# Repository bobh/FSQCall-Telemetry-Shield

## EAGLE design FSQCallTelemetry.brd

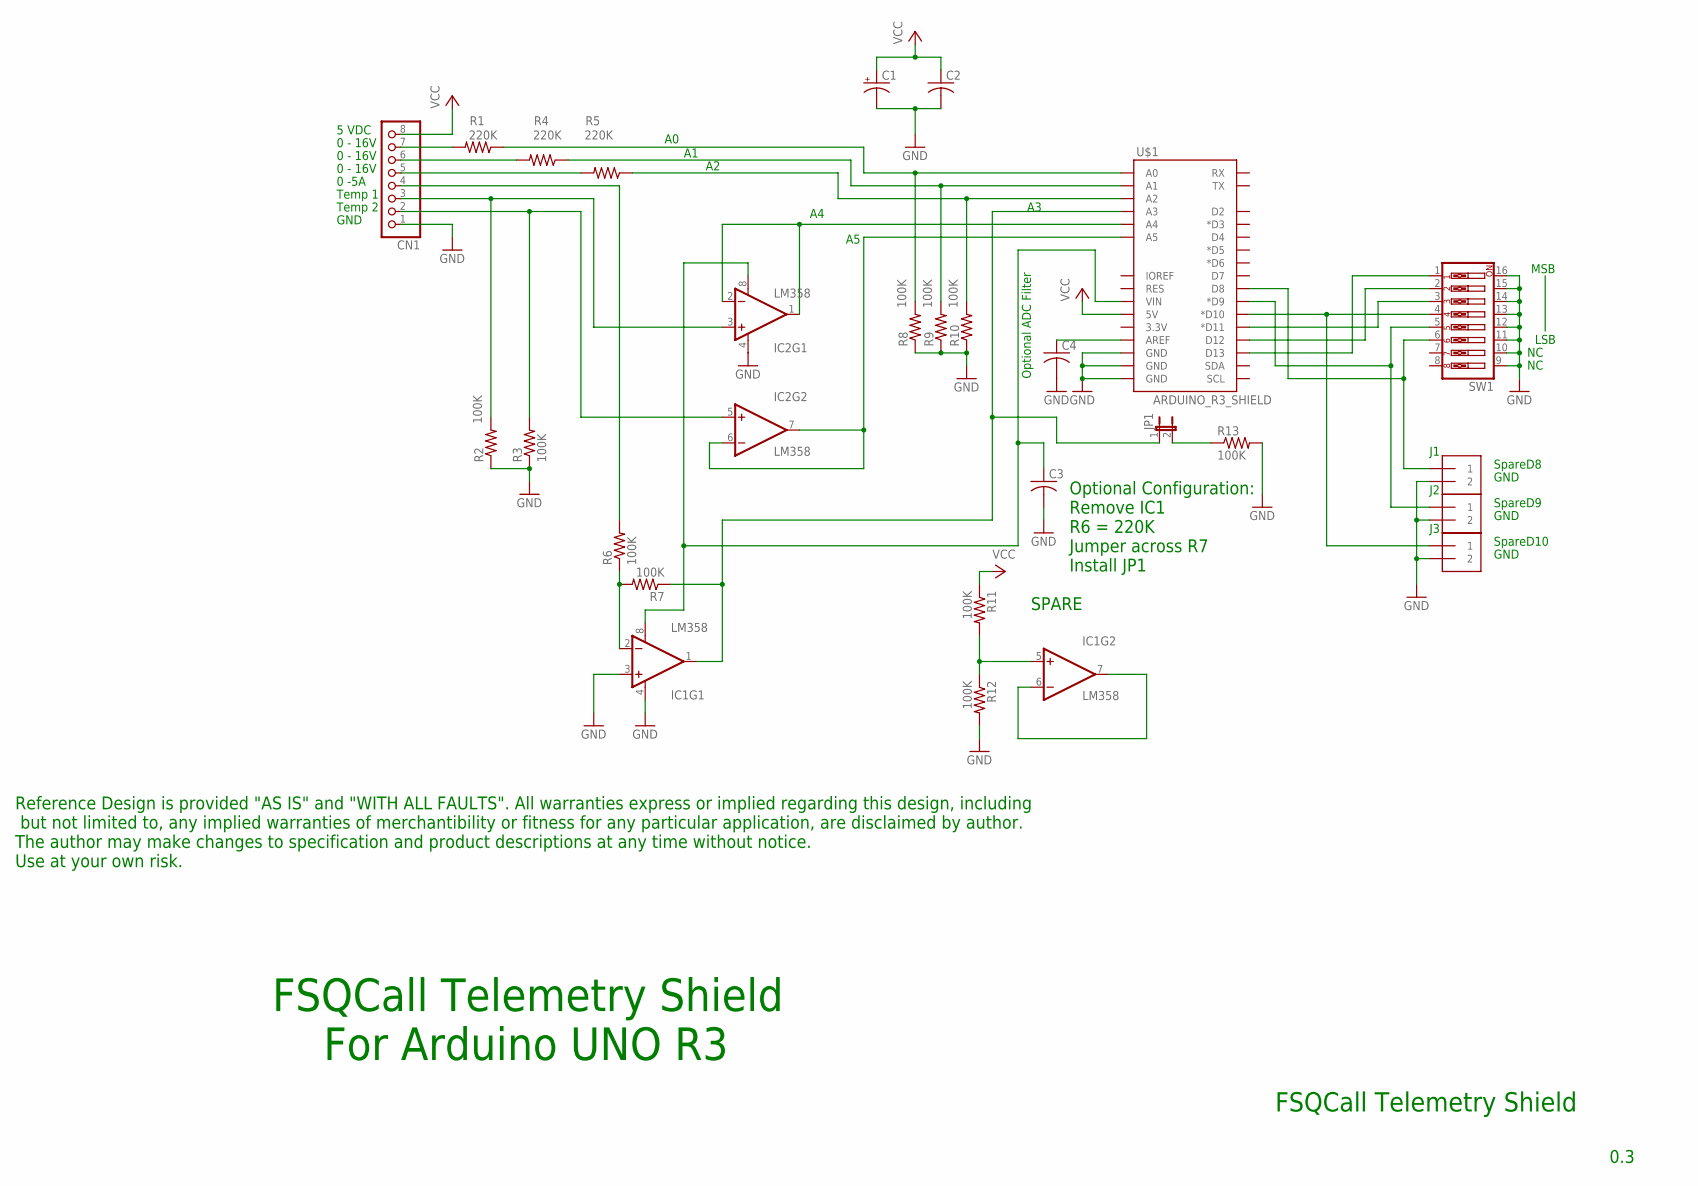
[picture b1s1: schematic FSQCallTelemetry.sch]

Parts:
C1: CPOL-USTT6D6; TT5D6
C2, C3, C4: C-US050-025X075; C050-025X075
CN1: PINHD-1X8BIG; 1X08-BIG
IC1, IC2: LM358; DIP08
J1, J2, J3: 1X2-3.5MM
JP1: JP1E; JP1
R1, R4, R5: 220K; 0207/10
R2, R3, R6, R7, R8, R9, R10, R11, R12, R13: 100K; 0207/10
SW1: SW_DIP-8; DIPSWITCH-08
U$1: ARDUINO_R3_SHIELD; UNO_R3_SHIELD

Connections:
GND: C1.-, C2.2, C3.2, C4.2, CN1.1, IC1.3 (+IN), IC1.4 (V-), IC2.4 (V-), J1.2, J2.2, J3.2, R2.1, R3.1, R8.1, R9.1, R10.1, R12.2, R13.2, SW1.9, SW1.10, SW1.11, SW1.12, SW1.13, SW1.14, SW1.15, SW1.16, U$1.GND@0 (GND), U$1.GND@1 (GND), U$1.GND@2 (GND)
unnamed: CN1.2, IC2.5 (+IN), R3.2
unnamed: IC1.2 (-IN), R6.1, R7.2
unnamed: CN1.3, IC2.3 (+IN), R2.2
unnamed: IC2.6 (-IN), IC2.7 (OUT), U$1.A5
unnamed: CN1.4, R6.2
unnamed: C3.1, IC1.8 (V+), IC2.8 (V+), U$1.VIN
unnamed: C4.1, U$1.AREF
unnamed: SW1.1, U$1.D13
unnamed: CN1.7, R1.2
unnamed: R1.1, R8.2, U$1.A0
unnamed: R4.1, R9.2, U$1.A1
unnamed: R5.1, R10.2, U$1.A2
unnamed: SW1.2, U$1.D12
unnamed: IC1.1 (OUT), JP1.1, R7.1, U$1.A3
unnamed: IC2.1 (OUT), IC2.2 (-IN), U$1.A4
unnamed: SW1.3, U$1.D11 (*D11)
unnamed: J3.1, SW1.4, U$1.D10 (*D10)
unnamed: J2.1, SW1.5, U$1.D9 (*D9)
unnamed: IC1.5 (+IN), R11.2, R12.1
unnamed: IC1.6 (-IN), IC1.7 (OUT)
unnamed: J1.1, SW1.6, U$1.D8
unnamed: CN1.6, R4.2
unnamed: CN1.5, R5.2
unnamed: JP1.2, R13.1
VCC: C1.+, C2.1, CN1.8, R11.1, U$1.5V

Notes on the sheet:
Reference Design is provided "AS IS" and "WITH ALL FAULTS". All warranties express or implied regarding this design, including but not limited to, any implied warranties of merchantibility or fitness for any particular application, are disclaimed by author. The author may make changes to specificat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
FSQCall Telemetry Shield For Arduino UNO R3
0.3
FSQCall Telemetry Shield
SPARE
MSB
LSB
Temp 2
Temp 1
0 -5A
GND
0 - 16V
5 VDC
SpareD8
SpareD9
SpareD10
Optional ADC Filter
Optional Configuration: Remove IC1 R6 = 220K Jumper across R7 Install JP1

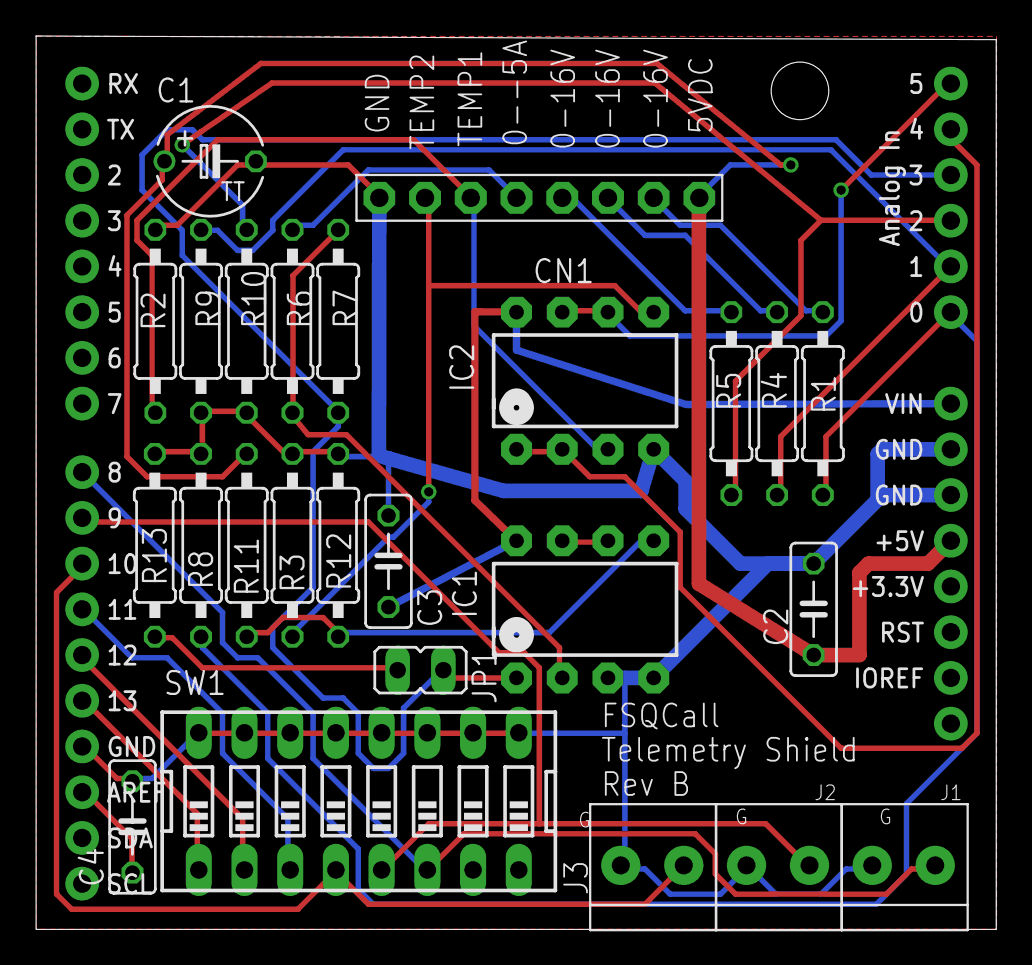
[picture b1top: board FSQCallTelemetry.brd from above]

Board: 2 copper layers, 53.3 x 49.6 mm, 26 parts (0 on the bottom side), 26 nets.

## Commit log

2016-07-31 FSQCall Rev B

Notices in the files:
parts and their libraries:
SparkFun-AnalogIC: Licensing:Creative Commons ShareAlike 4.0 International - https://creativecommons.org/licenses/by-sa/4.0
